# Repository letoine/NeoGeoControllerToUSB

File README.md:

NeoGeoControllerToUSB
=====================

Simple adapter that transforms a NeoGeo controller into a USB controller.

NeoGeo controller pinout
========================

NeoGeo controller connector is a DB15. NeoGeo controller only has four (4)
buttons (A, B, C, D). The D button is connected to pins 9 and 4, but the
console only cheks for pin 4. Pins 10 and 2 are not connected.

Some superguns uses a DB15 for the controller with a compatible pinout. These
superguns are using the non-connected pins to support games with more than
four buttons, like capcom games using the kick-harness.

DB15 pinout controller
-------------------------
\ 1 2  3  4  5  6  7  8 /
 \ 9 10 11 12 13 14 15 /
  --------------------

pin |    function    | comment
----|----------------|--------------
 1  | +5V            |
 2  | Down           |
 3  | Right          |
 4  | B button       | 
 5  | D button       |
 6  | Select         |
 7  | NC/Kick1       | Not connected on NeoGeo, used for kick in superguns.
 8  | GND            | 
 9  | Up             | 
10  | Left           | 
11  | A button       | 
12  | C button       | 
13  | Start          | 
14  | NC/Kick3       | Not connected on NeoGeo, used for kick in superguns.
15  | D button/Kick2 | Not read by console, used for kick in superguns.

ATMega pins/Controller mapping
=========================

 IO | DB-Pin |  button
----|--------|--------
PB0 |    4   |  B
PB1 |   12   |  C
PB2 |    5   |  D
PB3 |    6   |  Select
PB4 |   13   |  Start
PB5 |    7   |  Kick_1
PB6 |   14   |  Kick_3
PB7 |   15   |  D/Kick_2
PC2 |   11   |  A
PD0 |   10   |  Left
PD1 |    9   |  Up
PD2 |    -   |   -
PD3 |    -   |   -
PD4 |    2   |  Down
PD5 |    3   |  Right
PD6 |    -   |   -
PD7 |    -   |   -

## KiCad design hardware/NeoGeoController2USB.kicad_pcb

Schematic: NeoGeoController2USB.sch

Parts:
C1, C2: 22p
C3, C5: 100nf
C4: 1uf
CON1: AVR-ISP6; AVR-ISP-6
CON2: TTL_6
J1: USB
J2: DB15
R1, R2, R4, R5, R6: 22ohms
R3: 10K
U1: ATMEGA32U2-AU
X1: 16Mhz

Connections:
A_BUTTON: J2.11 (P111), U1.21
B_BUTTON: J2.4, R5.2
C_BUTTON: J2.12, R4.2
DOWN: J2.2, U1.18
D_BUTTON: J2.5, U1.14
D_KICK_2: J2.15, U1.7
GND: C1.2, C2.2, C3.1, C4.1, C5.2, CON1.6 (GND), CON2.1 (GND), J1.4 (GND), J1.5 (Shield_1), J1.6 (Shield_2), J2.8, U1.3, U1.28
KICK_1: J2.7, U1.10
KICK_3: J2.14, U1.6
LEFT: J2.10, U1.20
MISO: CON1.1 (MISO), R6.1, U1.17
MOSI: CON1.4 (MOSI), R5.1, U1.16
unnamed: J1.3 (D+), R2.1
unnamed: J1.2 (D-), R1.1
unnamed: R1.2, U1.30
unnamed: C4.2, U1.27
unnamed: CON2.4 (TX), U1.9
unnamed: CON2.2 (~CTS~), U1.13
unnamed: CON2.6 (~RTS~), U1.12
unnamed: CON2.5 (RX), U1.8
unnamed: R2.2, U1.29
unnamed: C1.1, U1.1, X1.1
unnamed: C2.1, U1.2, X1.2
RESET: C5.1, CON1.5 (RST), R3.2, U1.24
RIGHT: J2.3, R6.2
SCK: CON1.3 (SCK), R4.1, U1.15
SELECT: J2.6, U1.11
START: J2.13, U1.5
UP: J2.9, U1.19
VCC: C3.2, CON1.2 (VCC), CON2.3 (VCC), J1.1 (Vbus), J2.1, R3.1, U1.4, U1.31, U1.32

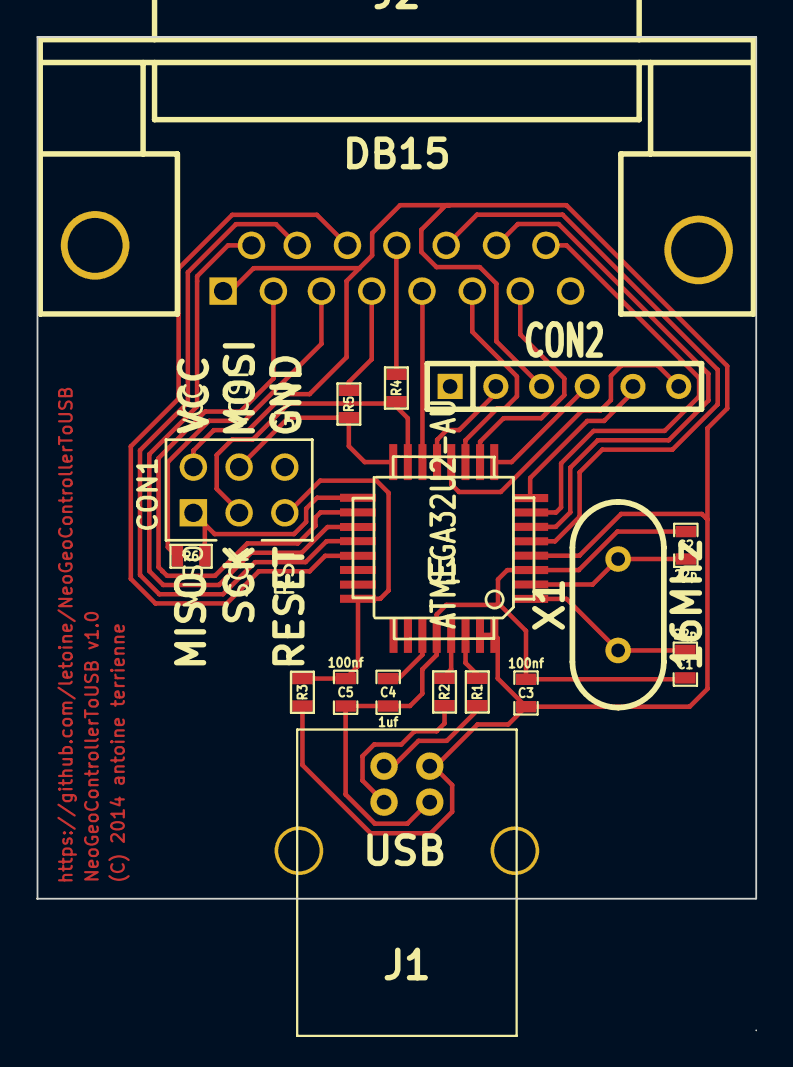
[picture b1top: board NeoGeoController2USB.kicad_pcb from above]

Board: 2 copper layers, 40.0 x 47.9 mm, 17 parts (0 on the bottom side), 30 nets.

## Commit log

2014-08-02 Update shematics. Work in progress.
2014-08-02 Adding pinout doc for NeoGeo controller.
2014-08-02 Discovering Markdown syntax.
2014-08-03 Board development in progress.
2014-08-03 First version fo the pcb.
2014-08-05 Shrinking board.
2014-09-07 Adding software.
2014-09-07 Adding license file for LUFA library.
2014-10-12 Adding access to serial port. Fix controller pinout numering.
2014-11-05 Adding serial debug to trace operation.
2014-12-09 Removing kicad temp files.

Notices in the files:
hardware/NeoGeoController2USB.kicad_pcb:
(C) 2014 antoine terrienne
